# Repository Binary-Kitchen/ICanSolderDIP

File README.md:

# I Can Solder - DIP
Very easy soldering kit for kids and beginners.

- Status: **Complete**
- Difficulty: **1/5**

### Parts List

| Amount | Name         | Description                        |
|--------|--------------|------------------------------------|
| 3      | LED1 - LED3  | LED 5mm rainbow RGB                |
| 1      |              | Battery holder                     |
| 1      |              | Buttefly pin                       |
| 1      |              | PCB                                |

### Manual
You can find the manual and pictures of every step here: https://github.com/Binary-Kitchen/SolderingTutorial

### Copyright and Authorship

- Board: [CC-BY-SA 4.0](https://creativecommons.org/licenses/by-sa/4.0/) - Thomas Basler, Timo Schindler
- CR2032 battery holder footprint: [CC-BY 4.0](https://creativecommons.org/licenses/by/4.0/) - Sparkfun (https://github.com/sparkfun/SparkFun-KiCad-Libraries)

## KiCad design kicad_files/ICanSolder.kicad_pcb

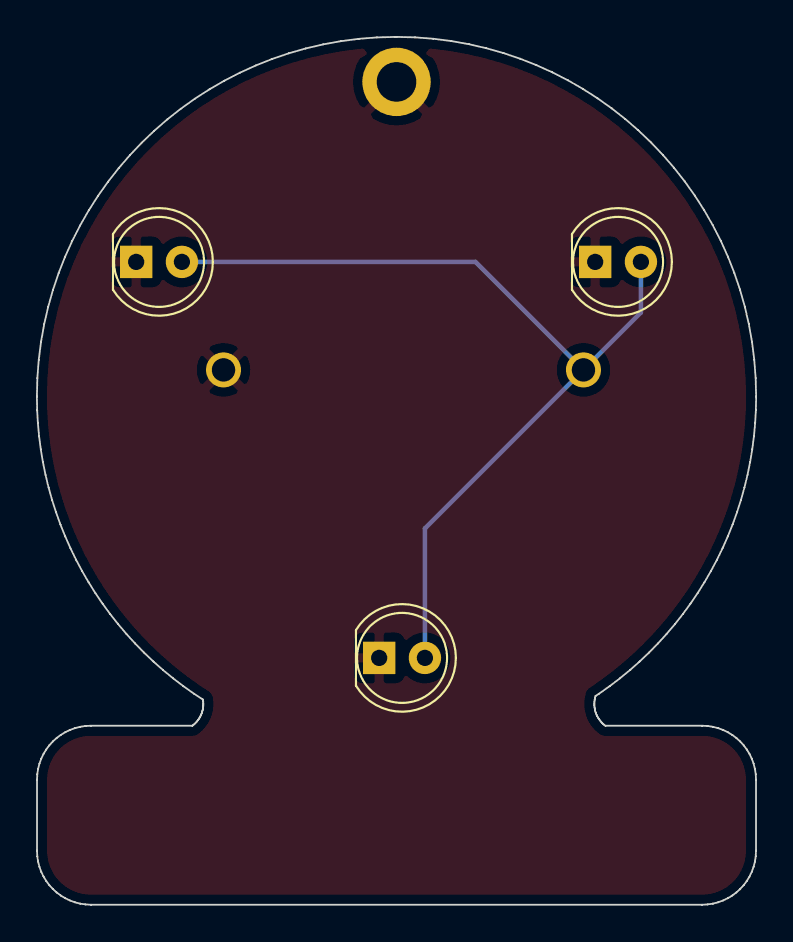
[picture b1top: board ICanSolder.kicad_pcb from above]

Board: 2 copper layers, 40.0 x 48.2 mm, 6 parts (1 on the bottom side), 2 nets.

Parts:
BT1: Battery_Cell; BATTCOM_20MM_PTH
D1, D2, D3: LED; LED_D5.0mm_Clear
H1: MountingHole_Pad; MountingHole_2.2mm_M2_DIN965_Pad
Ref**: Val**; binary_kitchen_logo_prepared

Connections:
GND: BT1.2, D1.1, D2.1, D3.1, H1.1
VCC: BT1.1, D1.2, D2.2, D3.2

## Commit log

2020-09-20 added original eagle files
2020-09-20 added some misc files for logo and outline
2020-09-20 first 2.0 version for layout
2020-09-20 added readme
2020-09-20 added license-file
2020-09-20 fixed path-error
2020-09-20 fixed table in readme
2020-09-20 minor changes
2020-09-20 added version number for license
2020-09-20 generated ibom
2020-09-20 added gerber files
2020-10-11 renamed folders
2021-04-20 fixed minor errors
